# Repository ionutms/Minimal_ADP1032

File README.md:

# Minimal_ADP1032

A minimalistic implementation of the ADP1032 IC.

## Dependencies

This project has the following dependencies:

### 1. KiCAD Symbols Generator

This repository uses [KiCAD_Symbols_Generator](https://github.com/ionutms/KiCAD_Symbols_Generator) as a submodule for custom symbol generation.

To initialize the submodule after cloning this repository:

```bash
git submodule update --init --recursive
```

### 2. 3D Models

This project requires the [3D_Models_Vault](https://github.com/ionutms/3D_Models_Vault) repository for 3D models.

#### Setup for KiCAD 9:

1. Clone the 3D models repository:
   ```bash
   git clone https://github.com/ionutms/3D_Models_Vault.git
   ```

2. In KiCAD 9, add an environment variable:
   - Variable name: `KICAD9_3D_MODELS_VAULT`
   - Variable value: Full path to where you cloned the 3D_Models_Vault repository

## Usage

After setting up the dependencies, open the project in KiCAD 9 to access all features including the 3D models.

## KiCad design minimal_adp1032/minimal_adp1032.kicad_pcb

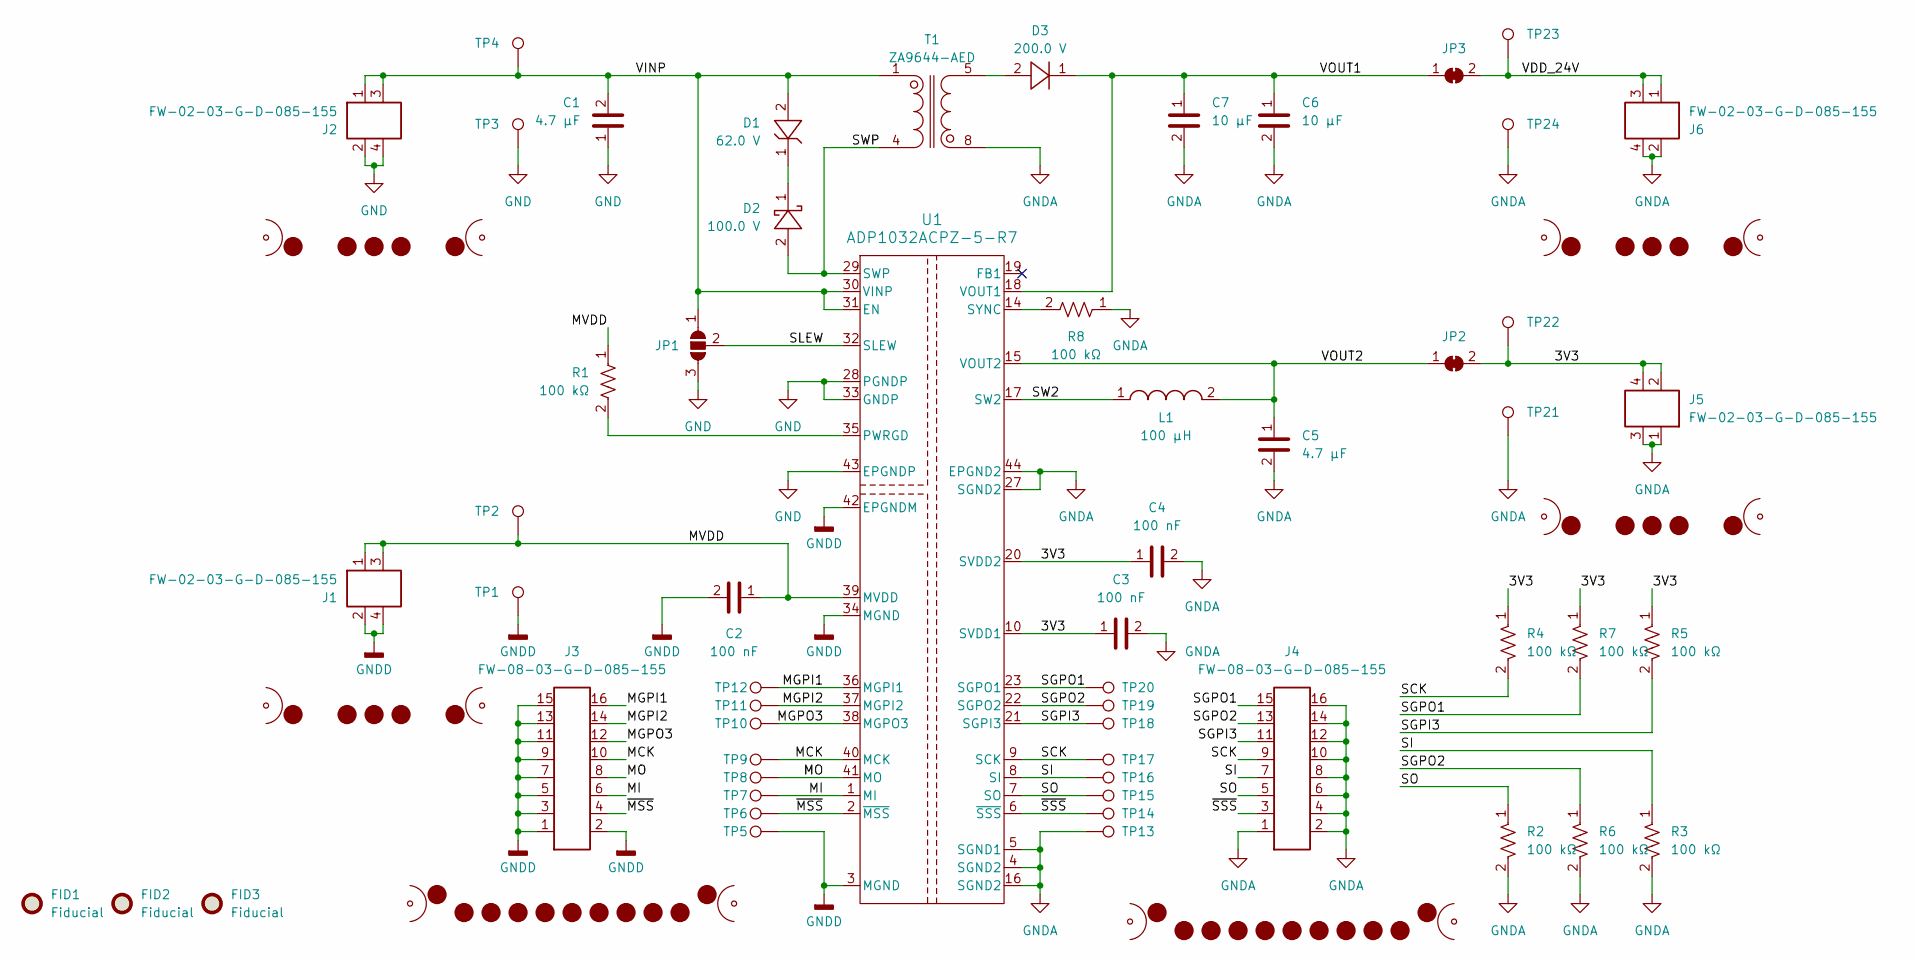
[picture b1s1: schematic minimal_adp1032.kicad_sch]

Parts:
C1: 4.7 µF; C_1210_200_3225Metric; Tolerance 10%; Voltage Rating 100V; MPN GCM32DC72A475KE02K
C2, C3, C4: 100 nF; C_0402_1005Metric; Voltage Rating DC 50 VDC; Tolerance 10%; MPN GCM155R71H104KE02D
C5: 4.7 µF; C_0603_1608Metric; Voltage Rating DC 10 VDC; Tolerance 10%; MPN C1608X7S1A475K080AC
C6, C7: 10 µF; C_1206_3216Metric; Voltage Rating DC 50 VDC; Tolerance 10%; MPN CL31B106KBHNNN#
D1: 62.0 V; SOD_123; MPN MMSZ5265BT1G
D2: 100.0 V; PowerDI_123; MPN DFLS1200-7
D3: 200.0 V; SOD_123F; MPN US1DWF
FID1, FID2, FID3: Fiducial; Fiducial_0.5mm_Mask1mm
J1, J2, J5, J6: FW-02-03-G-D-085-155; Current Rating (A) 5.2; Voltage Rating (V) 300; MPN FW-02-03-G-D-085-155
J3, J4: FW-08-03-G-D-085-155; Current Rating (A) 5.2; Voltage Rating (V) 300; MPN FW-08-03-G-D-085-155
JP1: SolderJumper_3_Open; SolderJumper-3_P1.3mm_Open_RoundedPad1.0x1.5mm_NumberLabels
JP2, JP3: SolderJumper_2_Bridged; SolderJumper-2_P1.3mm_Bridged_RoundedPad1.0x1.5mm
L1: 100 µH; XFL3012; Tolerance ±20%; MPN XFL3012-104ME
MB1, MB2, MB3, MB4: mouse-bite-midle-50mil-200mil; mouse-bite-50mil-305mil
MB5, MB6: mouse-bite-midle-50mil-200mil; mouse-bite-50mil-500mil
R1, R2, R3, R4, R5, R6, R7, R8: 100 kΩ; R_0402_1005Metric; Voltage Rating 50V; Tolerance 5%; MPN ERJ-2GEJ104X
T1: ZA9644-AED; ZA9644; Tolerance ±10%; MPN ZA9644-AED
TP1, TP2, TP3, TP4, TP5, TP6, TP7, TP8, TP9, TP10, TP11, TP12, TP13, TP14, TP15, TP16, TP17, TP18, TP19, TP20, TP21, TP22, TP23, TP24: TestPoint; TestPoint_THTPad_Castelated
U1: ADP1032ACPZ-5-R7; CP-41-1_ADI; MPN ADP1032ACPZ-5-R7

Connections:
/3V3: C3.1, C4.1, J5.2, J5.4, JP2.2, R4.1, R5.1, R7.1, TP22.1, U1.10 (SVDD1), U1.20 (SVDD2)
/MCK: J3.10, TP9.1, U1.40 (MCK)
/MGPI1: J3.16, TP12.1, U1.36 (MGPI1)
/MGPI2: J3.14, TP11.1, U1.37 (MGPI2)
/MGPO3: J3.12, TP10.1, U1.38 (MGPO3)
/MI: J3.6, TP7.1, U1.1 (MI)
/MO: J3.8, TP8.1, U1.41 (MO)
/MVDD: C2.1, J1.1, J1.3, R1.1, TP2.1, U1.39 (MVDD)
/SCK: J4.9, R4.2, TP17.1, U1.9 (SCK)
/SGPI3: J4.11, R5.2, TP18.1, U1.21 (SGPI3)
/SGPO1: J4.15, R7.2, TP20.1, U1.23 (SGPO1)
/SGPO2: J4.13, R6.1, TP19.1, U1.22 (SGPO2)
/SI: J4.7, R3.1, TP16.1, U1.8 (SI)
/SLEW: JP1.2 (C), U1.32 (SLEW)
/SO: J4.5, R2.1, TP15.1, U1.7 (SO)
/SW2: L1.1, U1.17 (SW2)
/SWP: D2.2, T1.4, U1.29 (SWP)
/VDD_24V: J6.1, J6.3, JP3.2, TP23.1
/VINP: C1.2, D1.2, J2.1, J2.3, JP1.1 (A), T1.1, TP4.1, U1.30 (VINP), U1.31 (EN)
/VOUT1: C6.1, C7.1, D3.1, JP3.1, U1.18 (VOUT1)
/VOUT2: C5.1, JP2.1, L1.2, U1.15 (VOUT2)
/~MSS: J3.4, TP6.1, U1.2 (~MSS)
/~SSS: J4.3, TP14.1, U1.6 (~SSS)
GND: C1.1, J2.2, J2.4, JP1.3 (B), TP3.1, U1.28 (PGNDP), U1.33 (GNDP), U1.43 (EPGNDP)
GNDA: C3.2, C4.2, C5.2, C6.2, C7.2, J4.1, J4.2, J4.4, J4.6, J4.8, J4.10, J4.12, J4.14, J4.16, J5.1, J5.3, J6.2, J6.4, R2.2, R3.2, R6.2, R8.1, T1.8, TP13.1, TP21.1, TP24.1, U1.4 (SGND2), U1.5 (SGND1), U1.16 (SGND2), U1.27 (SGND2), U1.44 (EPGND2)
GNDD: C2.2, J1.2, J1.4, J3.1, J3.2, J3.3, J3.5, J3.7, J3.9, J3.11, J3.13, J3.15, TP1.1, TP5.1, U1.3 (MGND), U1.34 (MGND), U1.42 (EPGNDM)
unnamed: D1.1, D2.1
unnamed: D3.2, T1.5
unnamed: R1.2, U1.35 (PWRGD)
unnamed: R8.2, U1.14 (SYNC)

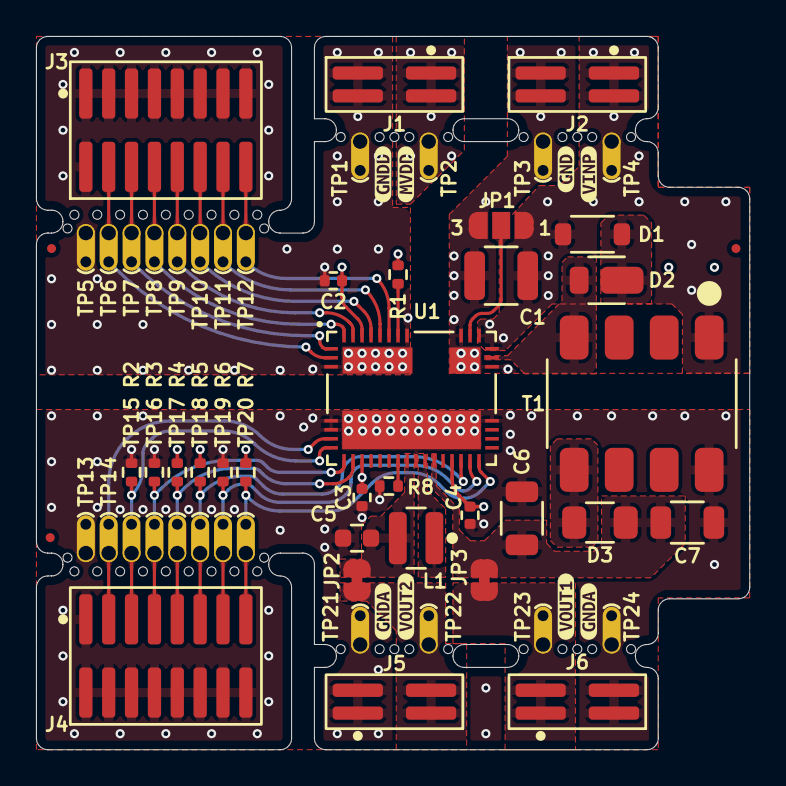
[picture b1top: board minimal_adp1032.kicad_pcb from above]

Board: 4 copper layers, 39.6 x 39.6 mm, 71 parts (0 on the bottom side), 30 nets.

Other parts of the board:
kibuzzard-1: G***; kibuzzard-678A0FCE
kibuzzard-2: G***; kibuzzard-679E3671
kibuzzard-3: G***; kibuzzard-678A0F1C
kibuzzard-4: G***; kibuzzard-678A0FC5
kibuzzard-5: G***; kibuzzard-679E35DB
kibuzzard-6: G***; kibuzzard-678A1049
kibuzzard-7: G***; kibuzzard-678A0E06
kibuzzard-8: G***; kibuzzard-678A1052

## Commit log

2025-01-08 Update clone and visitor statistics for 2025-01-08 15:09:33 EET
2025-01-08 Update clone and visitor statistics for 2025-01-08 18:31:58 EET
2025-01-09 create project and add libraries
2025-01-09 add initial work in progress project version
2025-01-09 use the latest submodule version
2025-01-09 update ADP1032ACPZ-5-R7 symbol
2025-01-09 development backup
2025-01-14 Add interactive bom files
2025-01-15 Update interactive bom files
2025-01-17 change form factor to be more compact
2025-01-17 update interactive bom
2025-01-17 generate schematics pdf
2025-01-17 minor updates
2025-01-18 minor changes
2025-01-18 Update clone and visitor statistics for 2025-01-18 13:18:01 EET
2025-01-28 Update subproject commit for KiCAD Symbol Generator
2025-01-29 Update VRML file path in KiCAD project configuration
2025-02-01 Update project configuration for improved compatibility
2025-02-08 Update project configuration for enhanced compatibility
2025-02-08 Add GLB 3D model
2025-02-12 Backup
2025-02-28 Update KiCAD Symbol Generator subproject and enhance component libraries
2025-03-04 Update minimal_adp1032 GLB model
2025-03-16 Remove KiCAD Symbol Generator submodule and associated configuration
2025-03-16 Add KiCAD Symbols Generator submodule and update configuration
2025-03-16 Update minimal_adp1032 footprint dimensions and adjust library paths for KiCAD Symbols Generator
2025-03-18 Switch to KiCad 9
2025-03-19 Add .log files to .gitignore
2025-03-19 Add project job set configuration for minimal_adp1032
2025-03-19 Update minimal_adp1032 project files and add side image
2025-03-19 Refactor project job set configuration for minimal_adp1032 to streamline 3D export settings
2025-03-19 Update binary files for minimal_adp1032 project
2025-03-20 Add output filename for log and new render command in project job set configuration
2025-03-20 Update subproject commit for KiCAD Symbols Generator
2025-03-20 Add new images and update project configuration for minimal_adp1032
2025-03-21 Update project job set configuration for minimal_adp1032 to enhance 3D export and rendering settings
2025-03-21 Remove obsolete images and add new 3D model and updated pictures for minimal_adp1032
2025-03-22 Update README.md to reflect project name change and clarify dependencies for minimal_ADP1032
2025-04-06 Update subproject commit for KiCAD Symbols Generator and add error check for text on edge cuts
2025-04-18 Update default zoom factor in KiCAD configuration
2025-04-18 Update KiCad documentation (schematics and PCB renders)
2025-04-25 Refactor KiCad configuration handling and update documentation generation workflow
2025-04-25 Remove unused schematic and image files for minimal ADP1032
2025-04-25 Update KiCad documentation for minimal_adp1032 (schematics and PCB renders)
2025-04-25 Adjust side view zoom and pan settings in KiCad configuration
2025-04-25 Adjust side view zoom factor in KiCad configuration
2025-08-18 Add bottom view rendering support and update file paths
2025-08-21 Add .github/.env to .gitignore
2025-08-21 Add GitHub Actions workflow to generate KiCad 3D models
2025-08-22 Update GitHub Actions workflows for KiCad model generation
2025-08-29 cleanup
2025-08-29 Update KiCAD workflow files
2025-10-05 Add trigger-symbol-check workflow and update generate_kicad_jobs
2025-10-05 Update KiCAD_Symbols_Generator submodule to latest commit
2025-10-05 chore: update workflows from central repository
2025-10-05 chore: update workflows and kicad config from central repository
2025-10-26 Update kicad-config workflow settings
